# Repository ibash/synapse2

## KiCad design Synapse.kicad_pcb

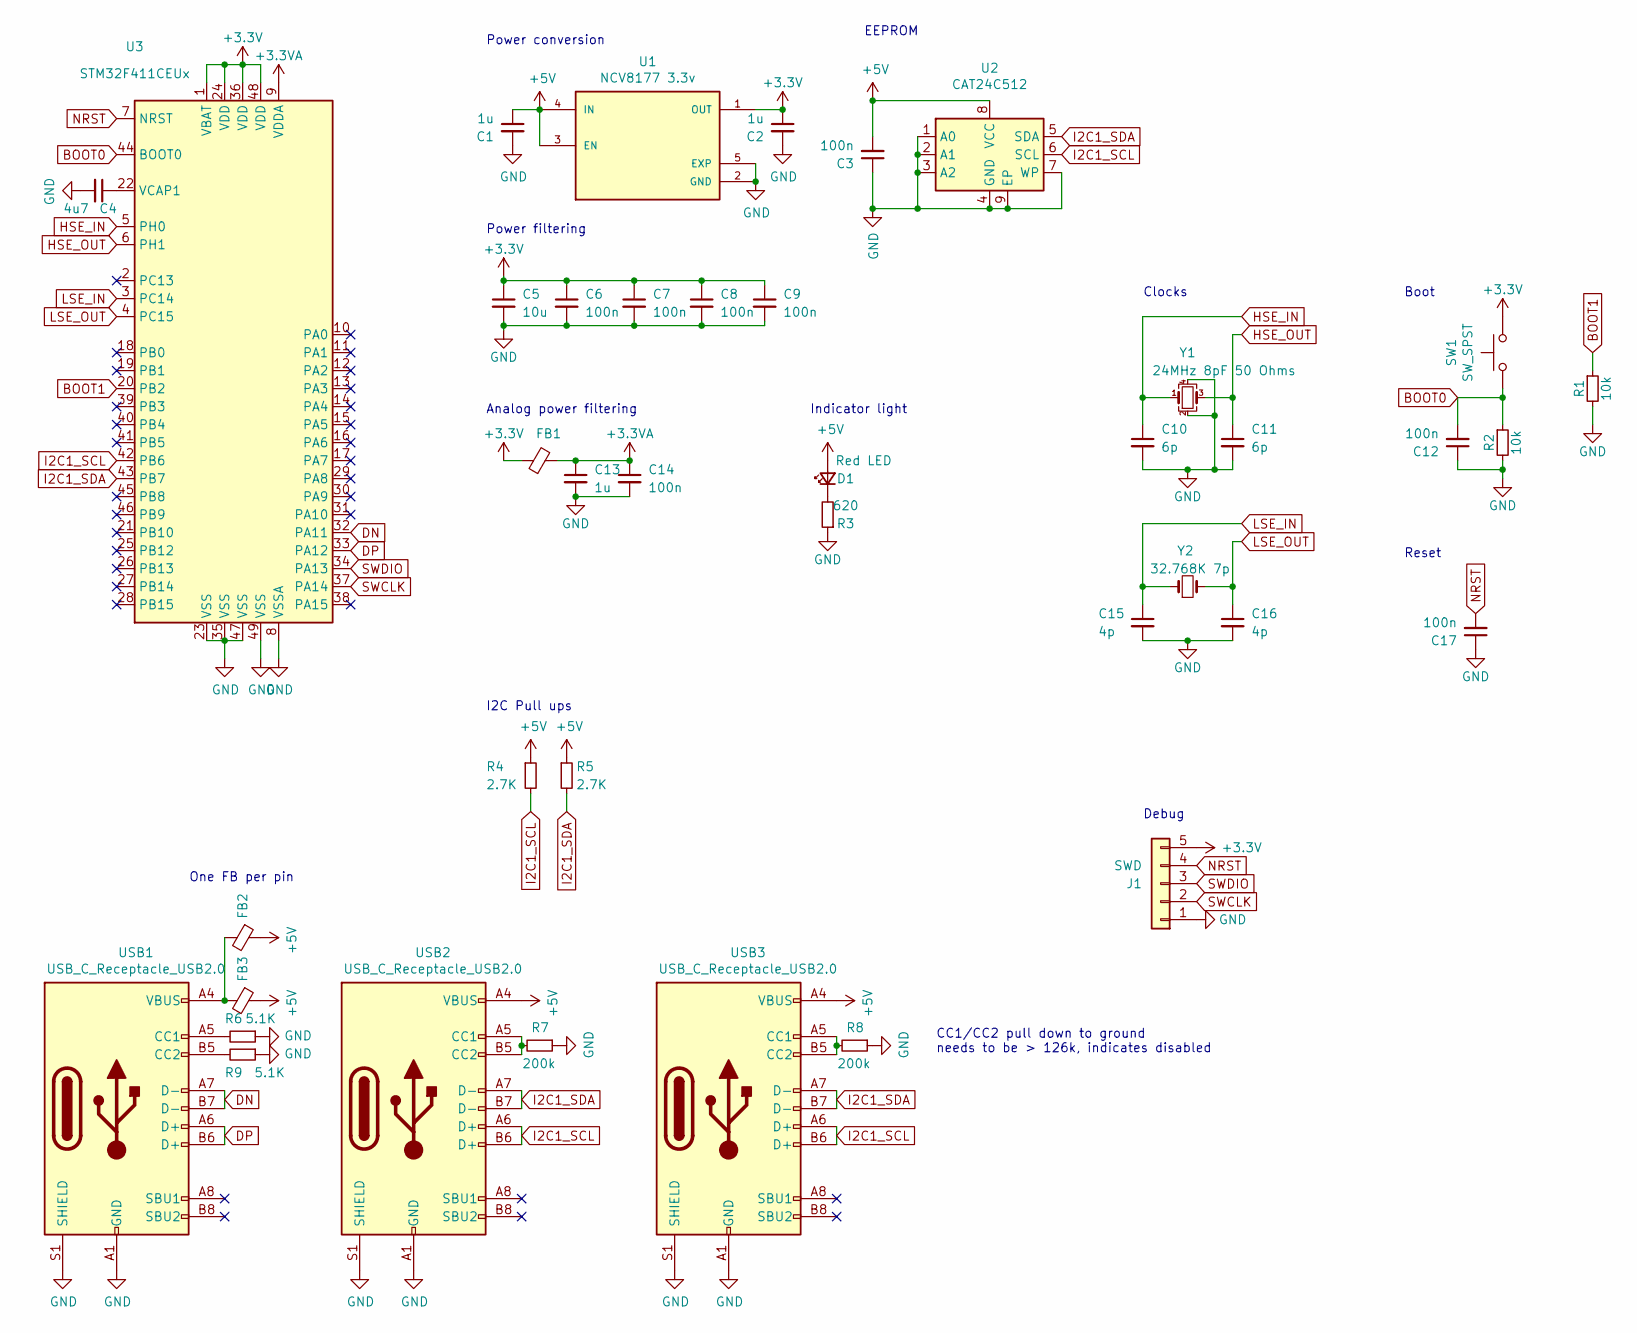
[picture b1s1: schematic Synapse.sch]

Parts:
C1, C2, C13: 1u; C_0402_1005Metric; LCSC C52923
C3, C6, C7, C8, C9, C12, C14, C17: 100n; C_0402_1005Metric; LCSC C1525
C4: 4u7; C_0402_1005Metric; LCSC C15525
C5: 10u; C_0603_1608Metric; LCSC C15525
C10, C11: 6p; C_0402_1005Metric; LCSC C30274
C15, C16: 4p; C_0402_1005Metric
D1: Red LED; LED_0402_1005Metric; LCSC C2286
FB1, FB2, FB3: 470 @ 100MHz; L_0402_1005Metric; LCSC C356977
J1: SWD; TestPoint_Pads_5x2.54_D1.5mm
R1, R2: 10k; R_0402_1005Metric; LCSC C25744
R3: 620; R_0402_1005Metric; LCSC C11702
R4, R5: 2.7K; R_0402_1005Metric; LCSC C25885
R6, R9: 5.1K; R_0402_1005Metric; LCSC C25905
R7, R8: 200k; R_0402_1005Metric; LCSC C25764
SW1: SW_SPST; SW_SPST_B3U-1000P; LCSC C231329
U1: NCV8177 3.3v; VREG_NCP170AMX300TCG; PARTREV A
U2: CAT24C512; CAT24C512HU5IGT3
U3: STM32F411CEUx; QFN-48-1EP_7x7mm_P0.5mm_EP5.6x5.6mm; LCSC C60420
USB1, USB2, USB3: USB_C_Receptacle_USB2.0; USB_C_Receptacle_HRO_TYPE-C-31-M-12; LCSC C165948
Y1: 24MHz 8pF 50 Ohms; Crystal_SMD_2016-4Pin_2.0x1.6mm
Y2: 32.768K 7p; Crystal_SMD_1210-2Pin_1.2x1.0mm

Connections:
+3.3VA: C13.1, C14.1, FB1.2, U3.9 (VDDA)
+3V3: C2.1, C5.1, C6.1, C7.1, C8.1, C9.1, FB1.1, J1.5, SW1.2, U1.1 (OUT), U3.1 (VBAT), U3.24 (VDD), U3.36 (VDD), U3.48 (VDD)
+5V: C1.1, C3.2, D1.2 (A), FB2.1, FB3.1, R4.1, R5.1, U1.3 (EN), U1.4 (IN), U2.8 (VCC), USB2.A4 (VBUS), USB2.A9 (VBUS), USB2.B4 (VBUS), USB2.B9 (VBUS), USB3.A4 (VBUS), USB3.A9 (VBUS), USB3.B4 (VBUS), USB3.B9 (VBUS)
BOOT0: C12.2, R2.1, SW1.1, U3.44 (BOOT0)
BOOT1: R1.1, U3.20 (PB2)
DN: U3.32 (PA11), USB1.A7 (D-), USB1.B7 (D-)
DP: U3.33 (PA12), USB1.A6 (D+), USB1.B6 (D+)
GND: C1.2, C2.2, C3.1, C4.2, C5.2, C6.2, C7.2, C8.2, C9.2, C10.2, C11.2, C12.1, C13.2, C14.2, C15.2, C16.2, C17.1, J1.1, R1.2, R2.2, R3.1, R6.1, R7.1, R8.1, R9.1, U1.2 (GND), U1.5 (EXP), U2.1 (A0), U2.2 (A1), U2.3 (A2), U2.4 (GND), U2.7 (WP), U2.9 (EP), U3.8 (VSSA), U3.23 (VSS), U3.35 (VSS), U3.47 (VSS), U3.49 (VSS), USB1.A1 (GND), USB1.A12 (GND), USB1.B1 (GND), USB1.B12 (GND), USB1.S1 (SHIELD), USB2.A1 (GND), USB2.A12 (GND), USB2.B1 (GND), USB2.B12 (GND), USB2.S1 (SHIELD), USB3.A1 (GND), USB3.A12 (GND), USB3.B1 (GND), USB3.B12 (GND), USB3.S1 (SHIELD), Y1.2, Y1.4
HSE_IN: C10.1, U3.5 (PH0), Y1.1
HSE_OUT: C11.1, U3.6 (PH1), Y1.3
I2C1_SCL: R4.2, U2.6 (SCL), U3.42 (PB6), USB2.A6 (D+), USB2.B6 (D+), USB3.A6 (D+), USB3.B6 (D+)
I2C1_SDA: R5.2, U2.5 (SDA), U3.43 (PB7), USB2.A7 (D-), USB2.B7 (D-), USB3.A7 (D-), USB3.B7 (D-)
LSE_IN: C15.1, U3.3 (PC14), Y2.1
LSE_OUT: C16.1, U3.4 (PC15), Y2.2
NRST: C17.2, J1.4, U3.7 (NRST)
unnamed: C4.1, U3.22 (VCAP1)
unnamed: D1.1 (K), R3.2
unnamed: FB2.2, FB3.2, USB1.A4 (VBUS), USB1.A9 (VBUS), USB1.B4 (VBUS), USB1.B9 (VBUS)
unnamed: R6.2, USB1.A5 (CC1)
unnamed: R7.2, USB2.A5 (CC1), USB2.B5 (CC2)
unnamed: R8.2, USB3.A5 (CC1), USB3.B5 (CC2)
unnamed: R9.2, USB1.B5 (CC2)
SWCLK: J1.2, U3.37 (PA14)
SWDIO: J1.3, U3.34 (PA13)

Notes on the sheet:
Clocks
Indicator light
EEPROM
Analog power filtering
Power filtering
Power conversion
CC1/CC2 pull down to ground needs to be > 126k, indicates disabled
I2C Pull ups
Reset
Debug
One FB per pin
Boot

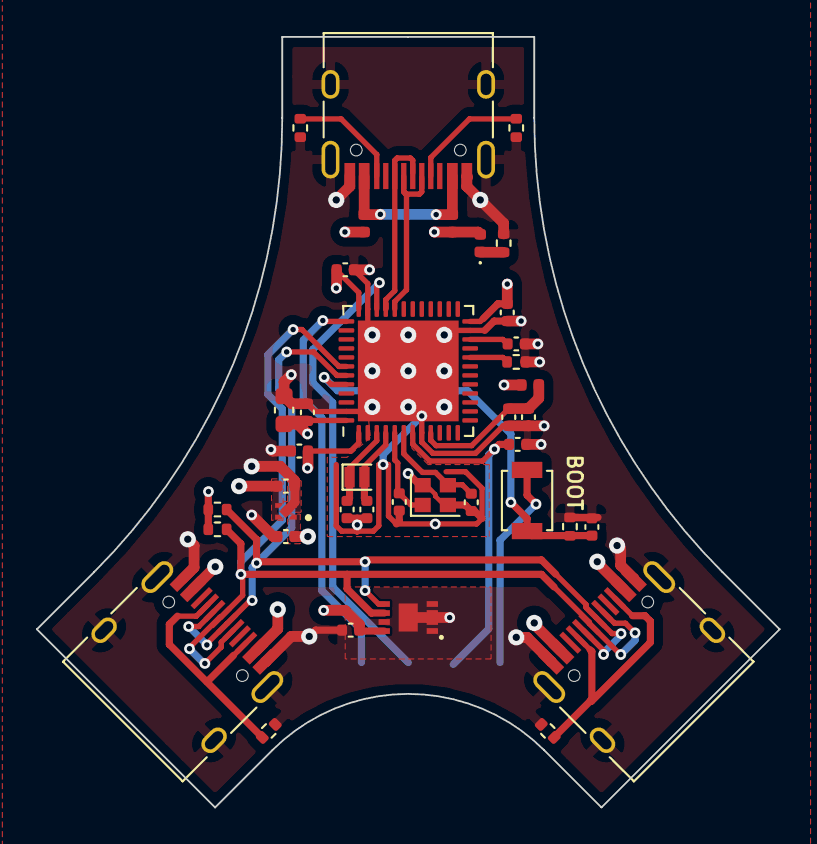
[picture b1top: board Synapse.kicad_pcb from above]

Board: 4 copper layers, 41.3 x 42.8 mm, 40 parts (1 on the bottom side), 24 nets.

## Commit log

2021-07-18 PAUSED: Use `git resume` to continue working.
2021-07-26 Synapse V2.0
    * Fully intergrates the STM32F411
    * Includes eeprom
    * Does not include a digital side switch button, couldn't make enough
    room
2021-07-26 More layout-ing, added copper pours, etc
2021-07-27 Small cleanups
2021-08-04 Final form
2021-08-04 vegeta
2021-08-04 New edge cuts
2021-08-15 Final synapse 2 with digikey components
